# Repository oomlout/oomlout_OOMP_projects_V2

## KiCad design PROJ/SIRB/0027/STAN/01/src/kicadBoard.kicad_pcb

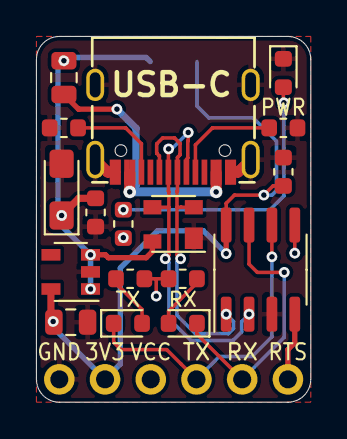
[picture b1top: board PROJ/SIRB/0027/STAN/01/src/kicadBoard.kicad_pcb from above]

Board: 2 copper layers, 15.2 x 20.3 mm, 19 parts (1 on the bottom side), 15 nets.

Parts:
C1, C4: 100nF; C_0603_1608Metric
C3: 22uF; CP_EIA-3216-18_Kemet-A_Pad1.58x1.35mm_HandSolder
C7: 10uF; C_0805_2012Metric
D1: PRTR5V0U2X; SOT-143
F1: 500mA; R_0805_2012Metric
J2: Conn_01x06; PinHeader_1x06_P2.54mm_Horizontal
PWR: BLUE; LED_0603_1608Metric
R1, R2, R3: 1K; R_0603_1608Metric
R4, R5: 5K1; R_0603_1608Metric
RX1: GREEN; LED_0603_1608Metric
TX2: RED; LED_0603_1608Metric
U1: CH330N; SOIC-8_3.9x4.9mm_P1.27mm
U2: AP2127K-3.3; SOT-23-5
USB-C: USB_C_Plug_USB2.0; USB_C
VCC: SolderJumper_3_Open; SolderJumper-3_P1.3mm_Open_RoundedPad1.0x1.5mm

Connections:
3V3: C1.2, C7.1, J2.5, U1.8, U2.5, VCC.3
D+: D1.2, U1.1, USB-C.A6, USB-C.B6
D-: D1.3, U1.2, USB-C.A7, USB-C.B7
GND: C1.1, C3.2, C4.2, C7.2, D1.1, J2.6, PWR.1, R4.2, R5.2, U1.3, U2.2, USB-C.A1, USB-C.A12, USB-C.B1, USB-C.B12, USB-C.S1
unnamed: F1.2, USB-C.A4, USB-C.A9, USB-C.B4, USB-C.B9
unnamed: R5.1, USB-C.A5
unnamed: R4.1, USB-C.B5
unnamed: PWR.2, R1.2
unnamed: R2.2, TX2.2
unnamed: R3.2, RX1.2
RTS: J2.1, U1.4
RX: J2.2, RX1.1, U1.7
TX: J2.3, TX2.1, U1.6
VBUS: C3.1, C4.1, D1.4, F1.1, U2.1, U2.3, VCC.1
VCC: J2.4, R1.1, R2.1, R3.1, U1.5, VCC.2

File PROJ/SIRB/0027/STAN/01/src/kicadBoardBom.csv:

"Id";"Designator";"Package";"Quantity";"Designation";"Supplier and ref";
1;"G***";"OSHW36x26";1;"LOGO";;;
2;"G***";"logo63x89";1;"LOGO";;;
3;"G***";"SirBoard112x35";1;"LOGO";;;
4;"J2";"PinHeader_1x06_P2.54mm_Horizontal";1;"Conn_01x06";;;
5;"PWR";"LED_0603_1608Metric";1;"BLUE";;;
6;"F1";"R_0805_2012Metric";1;"500mA";;;
7;"USB-C";"USB_C";1;"USB_C_Plug_USB2.0";;;
8;"R5,R4";"R_0603_1608Metric";2;"5K1";;;
9;"U1";"SOIC-8_3.9x4.9mm_P1.27mm";1;"CH330N";;;
10;"D1";"SOT-143";1;"PRTR5V0U2X";;;
11;"C1,C4";"C_0603_1608Metric";2;"100nF";;;
12;"TX2";"LED_0603_1608Metric";1;"RED";;;
13;"RX1";"LED_0603_1608Metric";1;"GREEN";;;
14;"R3,R2,R1";"R_0603_1608Metric";3;"1K";;;
15;"C7";"C_0805_2012Metric";1;"10uF";;;
16;"U2";"SOT-23-5";1;"AP2127K-3.3";;;
17;"C3";"CP_EIA-3216-18_Kemet-A_Pad1.58x1.35mm_HandSolder";1;"22uF";;;

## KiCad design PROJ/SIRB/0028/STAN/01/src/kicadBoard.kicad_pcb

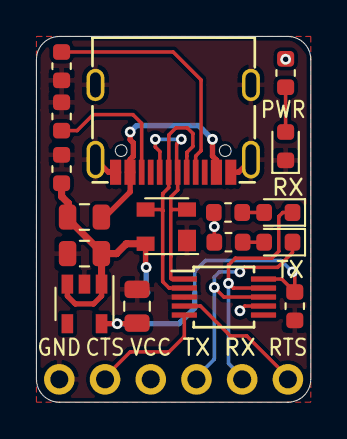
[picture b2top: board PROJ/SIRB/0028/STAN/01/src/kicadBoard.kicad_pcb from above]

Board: 2 copper layers, 15.2 x 20.3 mm, 19 parts (1 on the bottom side), 16 nets.

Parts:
C1, C4: 100nF; C_0603_1608Metric
C6, C7: 10uF; C_0805_2012Metric
D1: PRTR5V0U2X; SOT-143
F1: 500mA; Fuse_0805_2012Metric
J2: Conn_01x06; PinHeader_1x06_P2.54mm_Horizontal
P1: USB_C_Plug_USB2.0; USB_C
PWR: RED; LED_0603_1608Metric
R1, R2, R3: 1K; R_0603_1608Metric
R4, R5: 5K1; R_0603_1608Metric
RX1: GREEN; LED_0603_1608Metric
TX1: GREEN; LED_0603_1608Metric
U1: CH340E; MSOP-10_3x3mm_P0.5mm
U2: AP2127K-3.3; SOT-23-5
VCC: SolderJumper_3_Open; SolderJumper-3_P1.3mm_Open_RoundedPad1.0x1.5mm

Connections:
3V3: C1.2, C7.1, U1.10, U2.5, VCC.3
CTS: J2.5, U1.5
D+: D1.2, P1.A6, P1.B6, U1.1
D-: D1.3, P1.A7, P1.B7, U1.2
GND: C1.1, C4.2, C6.2, C7.2, D1.1, J2.6, P1.A1, P1.A12, P1.B1, P1.B12, P1.S1, PWR.1, R4.2, R5.2, U1.3, U2.2
unnamed: F1.2, P1.A4, P1.A9, P1.B4, P1.B9
unnamed: P1.A5, R5.1
unnamed: P1.B5, R4.1
unnamed: PWR.2, R1.2
unnamed: R2.2, TX1.2
unnamed: R3.2, RX1.2
RTS: J2.1, U1.4
RX: J2.2, RX1.1, U1.9
TX: J2.3, TX1.1, U1.8
VBUS: C4.1, C6.1, D1.4, F1.1, U2.1, U2.3, VCC.1
VCC: J2.4, R1.1, R2.1, R3.1, U1.7, VCC.2

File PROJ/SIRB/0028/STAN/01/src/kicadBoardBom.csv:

"Id";"Designator";"Package";"Quantity";"Designation";"Supplier and ref";
1;"G***";"OSHW36x26";1;"LOGO";;;
2;"G***";"logo63x89";1;"LOGO";;;
3;"G***";"SirBoard112x35";1;"LOGO";;;
4;"F1";"Fuse_0805_2012Metric";1;"500mA";;;
5;"J2";"PinHeader_1x06_P2.54mm_Horizontal";1;"Conn_01x06";;;
6;"P1";"USB_C";1;"USB_C_Plug_USB2.0";;;
7;"R5,R4";"R_0603_1608Metric";2;"5K1";;;
8;"D1";"SOT-143";1;"PRTR5V0U2X";;;
9;"U1";"MSOP-10_3x3mm_P0.5mm";1;"CH340E";;;
10;"C6,C7";"C_0805_2012Metric";2;"10uF";;;
11;"C1,C4";"C_0603_1608Metric";2;"100nF";;;
12;"PWR";"LED_0603_1608Metric";1;"RED";;;
13;"TX1,RX1";"LED_0603_1608Metric";2;"GREEN";;;
14;"R3,R2,R1";"R_0603_1608Metric";3;"1K";;;
15;"U2";"SOT-23-5";1;"AP2127K-3.3";;;

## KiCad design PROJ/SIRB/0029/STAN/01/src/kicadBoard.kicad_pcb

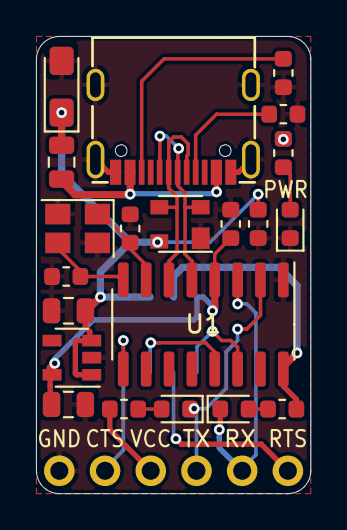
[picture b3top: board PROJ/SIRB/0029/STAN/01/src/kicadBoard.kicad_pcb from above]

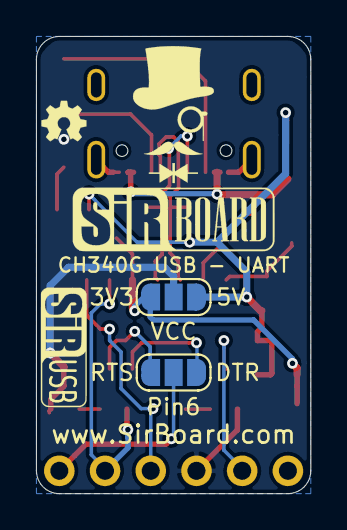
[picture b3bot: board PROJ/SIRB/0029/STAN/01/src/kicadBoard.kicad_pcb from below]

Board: 2 copper layers, 15.2 x 25.4 mm, 24 parts (2 on the bottom side), 20 nets.

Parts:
C1, C2: 9pF; C_0603_1608Metric
C3: 22uF; CP_EIA-3216-18_Kemet-A_Pad1.58x1.35mm_HandSolder
C4: 100nF; C_0603_1608Metric
C5: 10nF; C_0603_1608Metric
C6, C7: 10uF; C_0805_2012Metric
D1: PRTR5V0U2X; SOT-143
F1: 500mA; R_0805_2012Metric
J2: Conn_01x06; PinHeader_1x06_P2.54mm_Horizontal
P1: USB_C_Plug_USB2.0; USB_C
PWR: BLUE; LED_0603_1608Metric
Pin6: SolderJumper_3_Open; SolderJumper-3_P1.3mm_Open_RoundedPad1.0x1.5mm
R1, R2, R3: 1K; R_0603_1608Metric
R4, R5: 5K1; R_0603_1608Metric
RX1: GREEN; LED_0603_1608Metric
TX2: RED; LED_0603_1608Metric
U1: CH340G; SOIC-16_3.9x9.9mm_P1.27mm
U2: AP2127K-3.3; SOT-23-5
VCC: SolderJumper_3_Open; SolderJumper-3_P1.3mm_Open_RoundedPad1.0x1.5mm
Y1: Crystal_GND24; Crystal_SMD_SeikoEpson_TSX3225-4Pin_3.2x2.5mm

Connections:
3V3: C5.2, C7.1, U1.4, U2.5, VCC.3
CTS: J2.5, U1.9
D+: D1.2, P1.A6, P1.B6, U1.5
D-: D1.3, P1.A7, P1.B7, U1.6
DTR: Pin6.1, U1.13
GND: C1.2, C2.2, C3.2, C4.2, C5.1, C6.2, C7.2, D1.1, J2.6, P1.A1, P1.A12, P1.B1, P1.B12, P1.S1, PWR.1, R4.2, R5.2, U1.1, U2.2, Y1.2, Y1.4
unnamed: C1.1, U1.7, Y1.1
unnamed: C2.1, U1.8, Y1.3
unnamed: F1.2, P1.A4, P1.A9, P1.B4, P1.B9
unnamed: P1.A5, R5.1
unnamed: P1.B5, R4.1
unnamed: PWR.2, R1.2
unnamed: R2.2, TX2.2
unnamed: R3.2, RX1.2
P6: J2.1, Pin6.2
RTS: Pin6.3, U1.14
RX: J2.2, RX1.1, U1.3
TX: J2.3, TX2.1, U1.2
VBUS: C3.1, C4.1, C6.1, D1.4, F1.1, U2.1, U2.3, VCC.1
VCC: J2.4, R1.1, R2.1, R3.1, U1.16, VCC.2

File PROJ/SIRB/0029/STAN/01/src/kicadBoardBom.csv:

"Id";"Designator";"Package";"Quantity";"Designation";"Supplier and ref";
1;"G***";"OSHW36x26";1;"LOGO";;;
2;"G***";"SirBoard112x35";1;"LOGO";;;
3;"P1";"USB_C";1;"USB_C_Plug_USB2.0";;;
4;"J2";"PinHeader_1x06_P2.54mm_Horizontal";1;"Conn_01x06";;;
5;"G***";"SirUSB66x25";1;"LOGO";;;
6;"R1,R3,R2";"R_0603_1608Metric";3;"1K";;;
7;"R5,R4";"R_0603_1608Metric";2;"5K1";;;
8;"G***";"logo76x107";1;"LOGO";;;
9;"D1";"SOT-143";1;"PRTR5V0U2X";;;
10;"C2,C1";"C_0603_1608Metric";2;"9pF";;;
11;"PWR";"LED_0603_1608Metric";1;"BLUE";;;
12;"TX2";"LED_0603_1608Metric";1;"RED";;;
13;"RX1";"LED_0603_1608Metric";1;"GREEN";;;
14;"F1";"R_0805_2012Metric";1;"500mA";;;
15;"Y1";"Crystal_SMD_SeikoEpson_TSX3225-4Pin_3.2x2.5mm";1;"Crystal_GND24";;;
16;"C7,C6";"C_0805_2012Metric";2;"10uF";;;
17;"C5";"C_0603_1608Metric";1;"10nF";;;
18;"U2";"SOT-23-5";1;"AP2127K-3.3";;;
19;"U1";"SOIC-16_3.9x9.9mm_P1.27mm";1;"CH340G";;;
20;"C4";"C_0603_1608Metric";1;"100nF";;;
21;"C3";"CP_EIA-3216-18_Kemet-A_Pad1.58x1.35mm_HandSolder";1;"22uF";;;

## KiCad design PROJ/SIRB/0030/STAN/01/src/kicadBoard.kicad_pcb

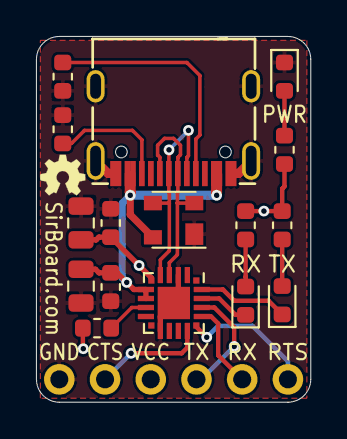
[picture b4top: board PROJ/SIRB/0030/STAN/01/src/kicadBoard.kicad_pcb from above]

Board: 2 copper layers, 15.2 x 20.3 mm, 17 parts (0 on the bottom side), 17 nets.

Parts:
C1, C4: 100nF; C_0603_1608Metric
C2, C5: 4.7uF; C_0805_2012Metric
D1: PRTR5V0U2X; SOT-143
J1: Conn_01x06; PinHeader_1x06_P2.54mm_Horizontal
P1: USB_C_Plug_USB2.0; USB_C
PWR: RED; LED_0603_1608Metric
R1, R3, R5, R6: 1K; R_0603_1608Metric
R2, R4: 5K1; R_0603_1608Metric
RX: GREEN; LED_0603_1608Metric
TX: GREEN; LED_0603_1608Metric
U1: CP2102N-A01-GQFN20; SiliconLabs_QFN-20-1EP_3x3mm_P0.5mm

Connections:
/CC1: P1.A5, R4.1
/CC2: P1.B5, R2.1
CTS: J1.5, U1.15
GND: C1.2, C2.2, C4.2, C5.2, D1.1, J1.6, P1.A1, P1.A12, P1.B1, P1.B12, P1.S1, PWR.1, R2.2, R4.2, U1.3, U1.12, U1.21
GPIO.2: TX.1, U1.20
GPIO.3: RX.1, U1.19
unnamed: PWR.2, R1.2
unnamed: R3.2, TX.2
unnamed: R5.2, RX.2
RST: R6.2, U1.9
RTS: J1.1, U1.16
RX: J1.2, U1.17
TX: J1.3, U1.18
VBUS: C1.1, C2.1, D1.4, P1.A4, P1.A9, P1.B4, P1.B9, U1.7, U1.8
VDD: C4.1, C5.1, J1.4, R1.1, R3.1, R5.1, R6.1, U1.6
uD+: D1.2, P1.A6, P1.B6, U1.4
uD-: D1.3, P1.A7, P1.B7, U1.5

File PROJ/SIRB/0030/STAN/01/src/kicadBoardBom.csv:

"Id";"Designator";"Package";"Quantity";"Designation";"Supplier and ref";
1;"G***";"OSHW36x26";1;"LOGO";;;
2;"G***";"logo76x107";1;"LOGO";;;
3;"G***";"SirBoard127x40";1;"LOGO";;;
4;"C1,C4";"C_0603_1608Metric";2;"100nF";;;
5;"U1";"SiliconLabs_QFN-20-1EP_3x3mm_P0.5mm";1;"CP2102N-A01-GQFN20";;;
6;"TX,RX";"LED_0603_1608Metric";2;"GREEN";;;
7;"C5,C2";"C_0805_2012Metric";2;"4.7uF";;;
8;"R4,R2";"R_0603_1608Metric";2;"5K1";;;
9;"D1";"SOT-143";1;"PRTR5V0U2X";;;
10;"R5,R6,R3,R1";"R_0603_1608Metric";4;"1K";;;
11;"P1";"USB_C";1;"USB_C_Plug_USB2.0";;;
12;"J1";"PinHeader_1x06_P2.54mm_Horizontal";1;"Conn_01x06";;;
13;"PWR";"LED_0603_1608Metric";1;"RED";;;

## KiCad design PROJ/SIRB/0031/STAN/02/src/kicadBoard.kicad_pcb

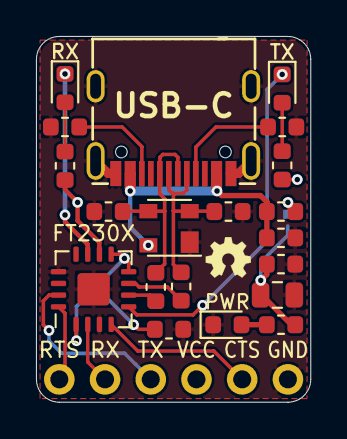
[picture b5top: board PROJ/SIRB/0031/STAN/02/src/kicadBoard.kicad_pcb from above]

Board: 2 copper layers, 15.2 x 20.3 mm, 22 parts (1 on the bottom side), 20 nets.

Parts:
C1: 10nF; C_0603_1608Metric
C2, C3: 47pF; C_0603_1608Metric
C4, C6: 100nF; C_0603_1608Metric
C5: 4.7uF; C_0805_2012Metric
D1: PRTR5V0U2X; SOT-143
FB1: 40E@100MHz; L_0603_1608Metric
J1: Conn_01x06; PinHeader_1x06_P2.54mm_Horizontal
JP1: SolderJumper_2_Open; SolderJumper-2_P1.3mm_Bridged_RoundedPad1.0x1.5mm
PWR: RED; LED_0603_1608Metric
R1, R2: 27e; R_0603_1608Metric
R3, R4, R5: 1k; R_0603_1608Metric
R6, R7: 5k1; R_0603_1608Metric
RX: GREEN; LED_0603_1608Metric
TX: GREEN; LED_0603_1608Metric
U1: FT230XQ; QFN-16-1EP_4x4mm_P0.65mm_EP2.1x2.1mm
USB-C: USB_C_Plug_USB2.0; USB_C

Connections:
CBUS1: RX.1, U1.11
CBUS2: TX.1, U1.5
CTS: J1.2, U1.4
D+: C2.1, D1.3, R2.2, USB-C.A6, USB-C.B6
D-: C3.1, D1.2, R1.1, USB-C.A7, USB-C.B7
GND: C1.2, C2.2, C3.2, C4.2, C5.2, C6.2, D1.1, J1.1, PWR.1, R6.2, R7.2, U1.3, U1.13, U1.17, USB-C.A1, USB-C.A12, USB-C.B1, USB-C.B12, USB-C.S1
unnamed: C6.1, U1.1, U1.8, U1.9
unnamed: FB1.1, JP1.1
unnamed: R7.1, USB-C.A5
unnamed: R6.1, USB-C.B5
unnamed: PWR.2, R4.2
unnamed: R3.2, TX.2
unnamed: R5.2, RX.2
RTS: J1.6, U1.16
RX: J1.5, U1.2
TX: J1.4, U1.15
VCC: C4.1, C5.1, J1.3, JP1.2, R3.1, R4.1, R5.1, U1.10
VUSB: C1.1, D1.4, FB1.2, USB-C.A4, USB-C.A9, USB-C.B4, USB-C.B9
uD+: R2.1, U1.6
uD-: R1.2, U1.7

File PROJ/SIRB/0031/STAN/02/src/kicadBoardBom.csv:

"Id";"Designator";"Package";"Quantity";"Designation";"Supplier and ref";
1;"G***";"OSHW36x26";1;"LOGO";;;
2;"D1";"SOT-143";1;"PRTR5V0U2X";;;
3;"R7,R6";"R_0603_1608Metric";2;"5k1";;;
4;"J1";"PinHeader_1x06_P2.54mm_Horizontal";1;"Conn_01x06";;;
5;"USB-C";"USB_C";1;"USB_C_Plug_USB2.0";;;
6;"C6,C4";"C_0603_1608Metric";2;"100nF";;;
7;"G***";"SirBoard98x31";1;"LOGO";;;
8;"G***";"logo63x89";1;"LOGO";;;
9;"R4,R3,R5";"R_0603_1608Metric";3;"1k";;;
10;"FB1";"L_0603_1608Metric";1;"40E@100MHz";;;
11;"C1";"C_0603_1608Metric";1;"10nF";;;
12;"TX,RX";"LED_0603_1608Metric";2;"GREEN";;;
13;"PWR";"LED_0603_1608Metric";1;"RED";;;
14;"C5";"C_0805_2012Metric";1;"4.7uF";;;
15;"U1";"QFN-16-1EP_4x4mm_P0.65mm_EP2.1x2.1mm";1;"FT230XQ";;;
16;"C3,C2";"C_0603_1608Metric";2;"47pF";;;
17;"R2,R1";"R_0603_1608Metric";2;"27e";;;

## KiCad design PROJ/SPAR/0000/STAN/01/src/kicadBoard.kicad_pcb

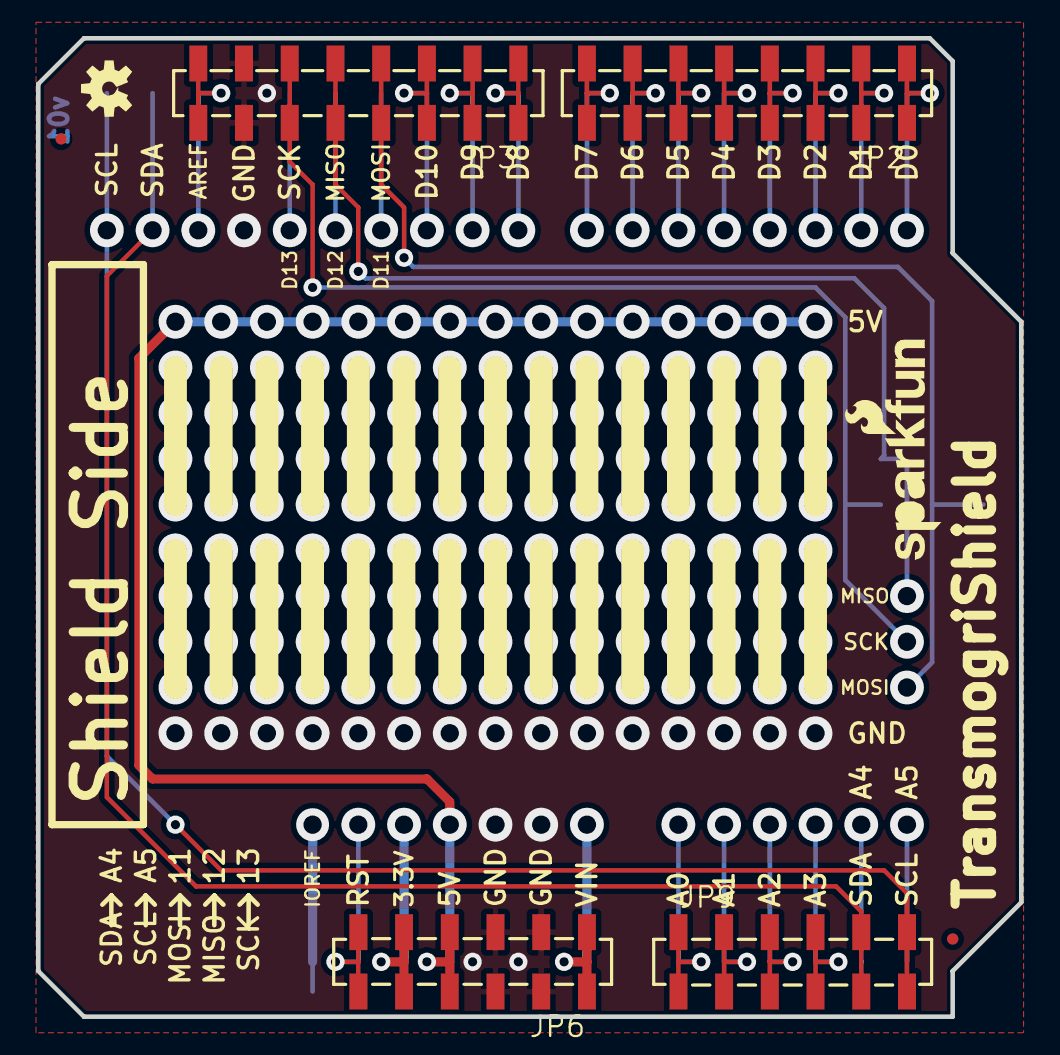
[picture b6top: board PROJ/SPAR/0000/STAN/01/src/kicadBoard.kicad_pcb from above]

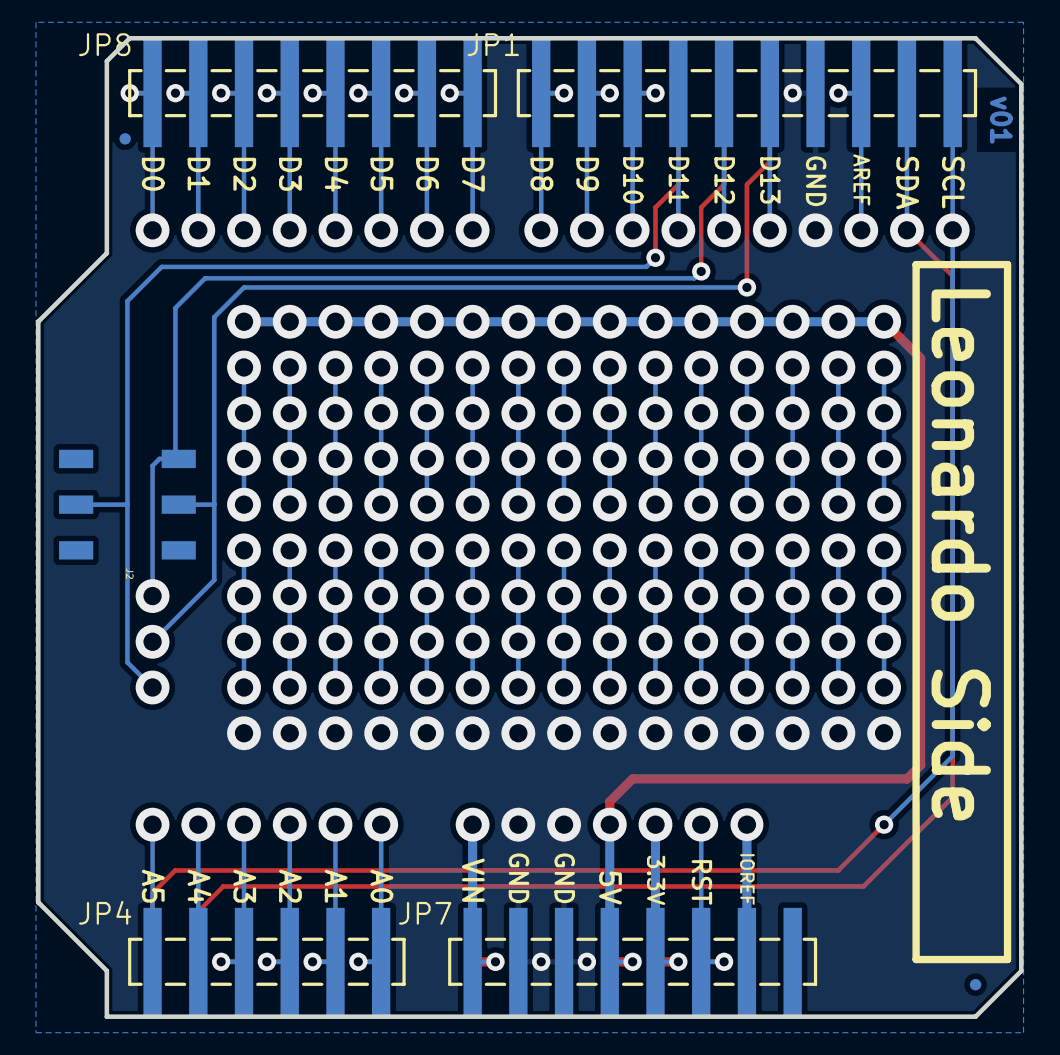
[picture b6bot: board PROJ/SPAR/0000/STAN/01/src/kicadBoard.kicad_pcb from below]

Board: 2 copper layers, 54.6 x 54.4 mm, 16 parts (7 on the bottom side), 26 nets.

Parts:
J2: Female; 2X3_SMD
JP1: Male; 1X10_SMD_MALE
JP2, JP3: Female; 1X08_SMD_COMBINED
JP4: Male; 1X06_SMD_MALE
JP5: LOGO-SFENW2; SFE-NEW-WEB
JP6, JP9: Female; 1X06_SMD_STRAIGHT_COMBO
JP7, JP8: Male; 1X08_SMD_MALE
JP10: LOGO-SFESK; SFE-LOGO-FLAME
JP11, JP12, JP13, JP14: FIDUCIALUFIDUCIAL; MICRO-FIDUCIAL
U$1: OSHW-LOGOS; OSHW-LOGO-S

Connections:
0: JP2.1, JP2.1@2, JP8.1
1: JP2.2, JP2.2@2, JP8.2
2: JP2.3, JP2.3@2, JP8.3
3: JP2.4, JP2.4@2, JP8.4
3.3V: JP6.5, JP6.5-2, JP7.5
4: JP2.5, JP2.5@2, JP8.5
5: JP2.6, JP2.6@2, JP8.6
5V: JP6.4, JP6.4-2, JP7.4
6: JP2.7, JP2.7@2, JP8.7
7: JP2.8, JP2.8@2, JP8.8
8: JP1.1, JP3.1, JP3.1@2
9: JP1.2, JP3.2, JP3.2@2
10: JP1.3, JP3.3, JP3.3@2
A0: JP4.P$6, JP9.1, JP9.1-2
A1: JP4.P$5, JP9.2, JP9.2-2
A2: JP4.P$4, JP9.3, JP9.3-2
A3: JP4.P$3, JP9.4, JP9.4-2
AREF: JP1.8, JP3.8, JP3.8@2
GND: JP1.7, JP3.7, JP3.7@2, JP6.2, JP6.2-2, JP6.3, JP6.3-2, JP7.2, JP7.3
MISO: J2.5, JP3.5, JP3.5@2
MOSI: J2.4, JP3.4, JP3.4@2
RESET: JP6.6, JP6.6-2, JP7.6
SCK: J2.3, JP3.6, JP3.6@2
SCL: JP1.10, JP9.6, JP9.6-2
SDA: JP1.9, JP9.5, JP9.5-2
VIN: JP6.1, JP6.1-2, JP7.1

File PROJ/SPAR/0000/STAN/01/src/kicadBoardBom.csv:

"Id";"Designator";"Package";"Quantity";"Designation";"Supplier and ref";
1;"JP9,JP6";"1X06_SMD_STRAIGHT_COMBO";2;"Female";;;
2;"JP10";"SFE-LOGO-FLAME";1;"LOGO-SFESK";;;
3;"U$1";"OSHW-LOGO-S";1;"OSHW-LOGOS";;;
4;"JP12,JP11,JP13,JP14";"MICRO-FIDUCIAL";4;"FIDUCIALUFIDUCIAL";;;
5;"JP2,JP3";"1X08_SMD_COMBINED";2;"Female";;;
6;"JP5";"SFE-NEW-WEB";1;"LOGO-SFENW2";;;
7;"J2";"2X3_SMD";1;"Female";;;
8;"JP7,JP8";"1X08_SMD_MALE";2;"Male";;;
9;"JP1";"1X10_SMD_MALE";1;"Male";;;
10;"JP4";"1X06_SMD_MALE";1;"Male";;;

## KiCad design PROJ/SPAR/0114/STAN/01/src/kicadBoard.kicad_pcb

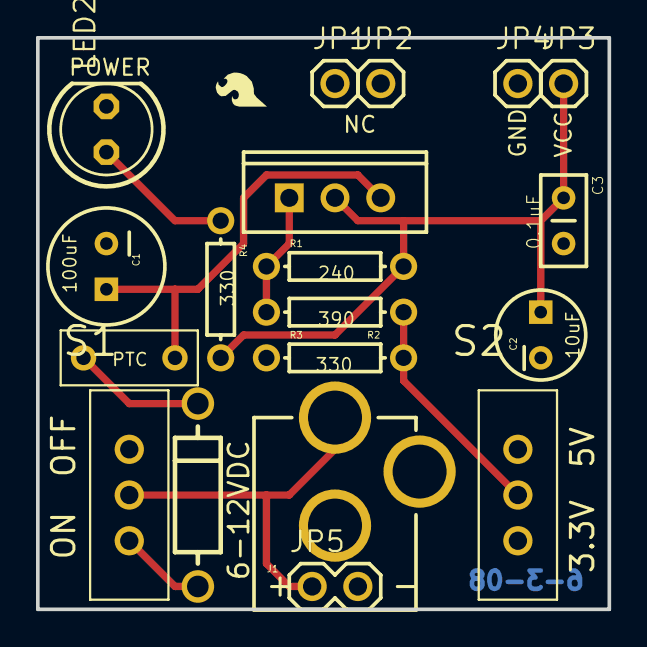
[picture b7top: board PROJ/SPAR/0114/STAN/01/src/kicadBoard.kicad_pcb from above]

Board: 2 copper layers, 31.8 x 31.8 mm, 20 parts (0 on the bottom side), 9 nets.

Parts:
C1: 100uF; CPOL-RADIAL-100UF-25V
C2: 10uF; CPOL-RADIAL-10UF-25V
C3: 0.1uF; CAP-PTH-SMALL2
D1: 1N4001; DIODE-0.4
F1: 500mA; PTC
J1: POWER_JACKPTH; POWER_JACK_PTH
JP1, JP2, JP3, JP4: 1X01
JP5: 1X02
LED2: Power; LED5MM
R1: 240; AXIAL-0.3
R2: 390; AXIAL-0.3
R3, R4: 330; AXIAL-0.3
S1: On/Off; SWITCH-SPST
S2: Voltage; SWITCH-SPST
U1: LM317; TO220-ADJ
U$1: LOGO-SFESK; SFE-LOGO-FLAME

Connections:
GND: C1.2, C2.2, C3.2, J1.GND, J1.GNDBREAK, JP4.1, JP5.2, LED2.K, R3.P$1, S2.3
unnamed: D1.C, F1.P$1
unnamed: D1.A, S1.3
unnamed: J1.PWR, JP5.1, S1.2
unnamed: R2.P$1, R3.P$2, S2.2
unnamed: R1.P$1, R2.P$2, U1.ADJ
unnamed: LED2.A, R4.P$1
RAW: C1.1, F1.P$2, U1.IN
VCC: C2.1, C3.1, JP3.1, R1.P$2, R4.P$2, U1.OUT

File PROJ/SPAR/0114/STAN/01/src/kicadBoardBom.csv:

"Id";"Designator";"Package";"Quantity";"Designation";"Supplier and ref";
1;"C3";"CAP-PTH-SMALL2";1;"0.1uF";;;
2;"R4,R3";"AXIAL-0.3";2;"330";;;
3;"C1";"CPOL-RADIAL-100UF-25V";1;"100uF";;;
4;"JP3,JP1,JP2,JP4";"1X01";4;"";;;
5;"U$1";"SFE-LOGO-FLAME";1;"LOGO-SFESK";;;
6;"LED2";"LED5MM";1;"Power";;;
7;"F1";"PTC";1;"500mA";;;
8;"U1";"TO220-ADJ";1;"LM317";;;
9;"R2";"AXIAL-0.3";1;"390";;;
10;"S1";"SWITCH-SPST";1;"On/Off";;;
11;"R1";"AXIAL-0.3";1;"240";;;
12;"S2";"SWITCH-SPST";1;"Voltage";;;
13;"D1";"DIODE-0.4";1;"1N4001";;;
14;"J1";"POWER_JACK_PTH";1;"POWER_JACKPTH";;;
15;"C2";"CPOL-RADIAL-10UF-25V";1;"10uF";;;
16;"JP5";"1X02";1;"";;;
